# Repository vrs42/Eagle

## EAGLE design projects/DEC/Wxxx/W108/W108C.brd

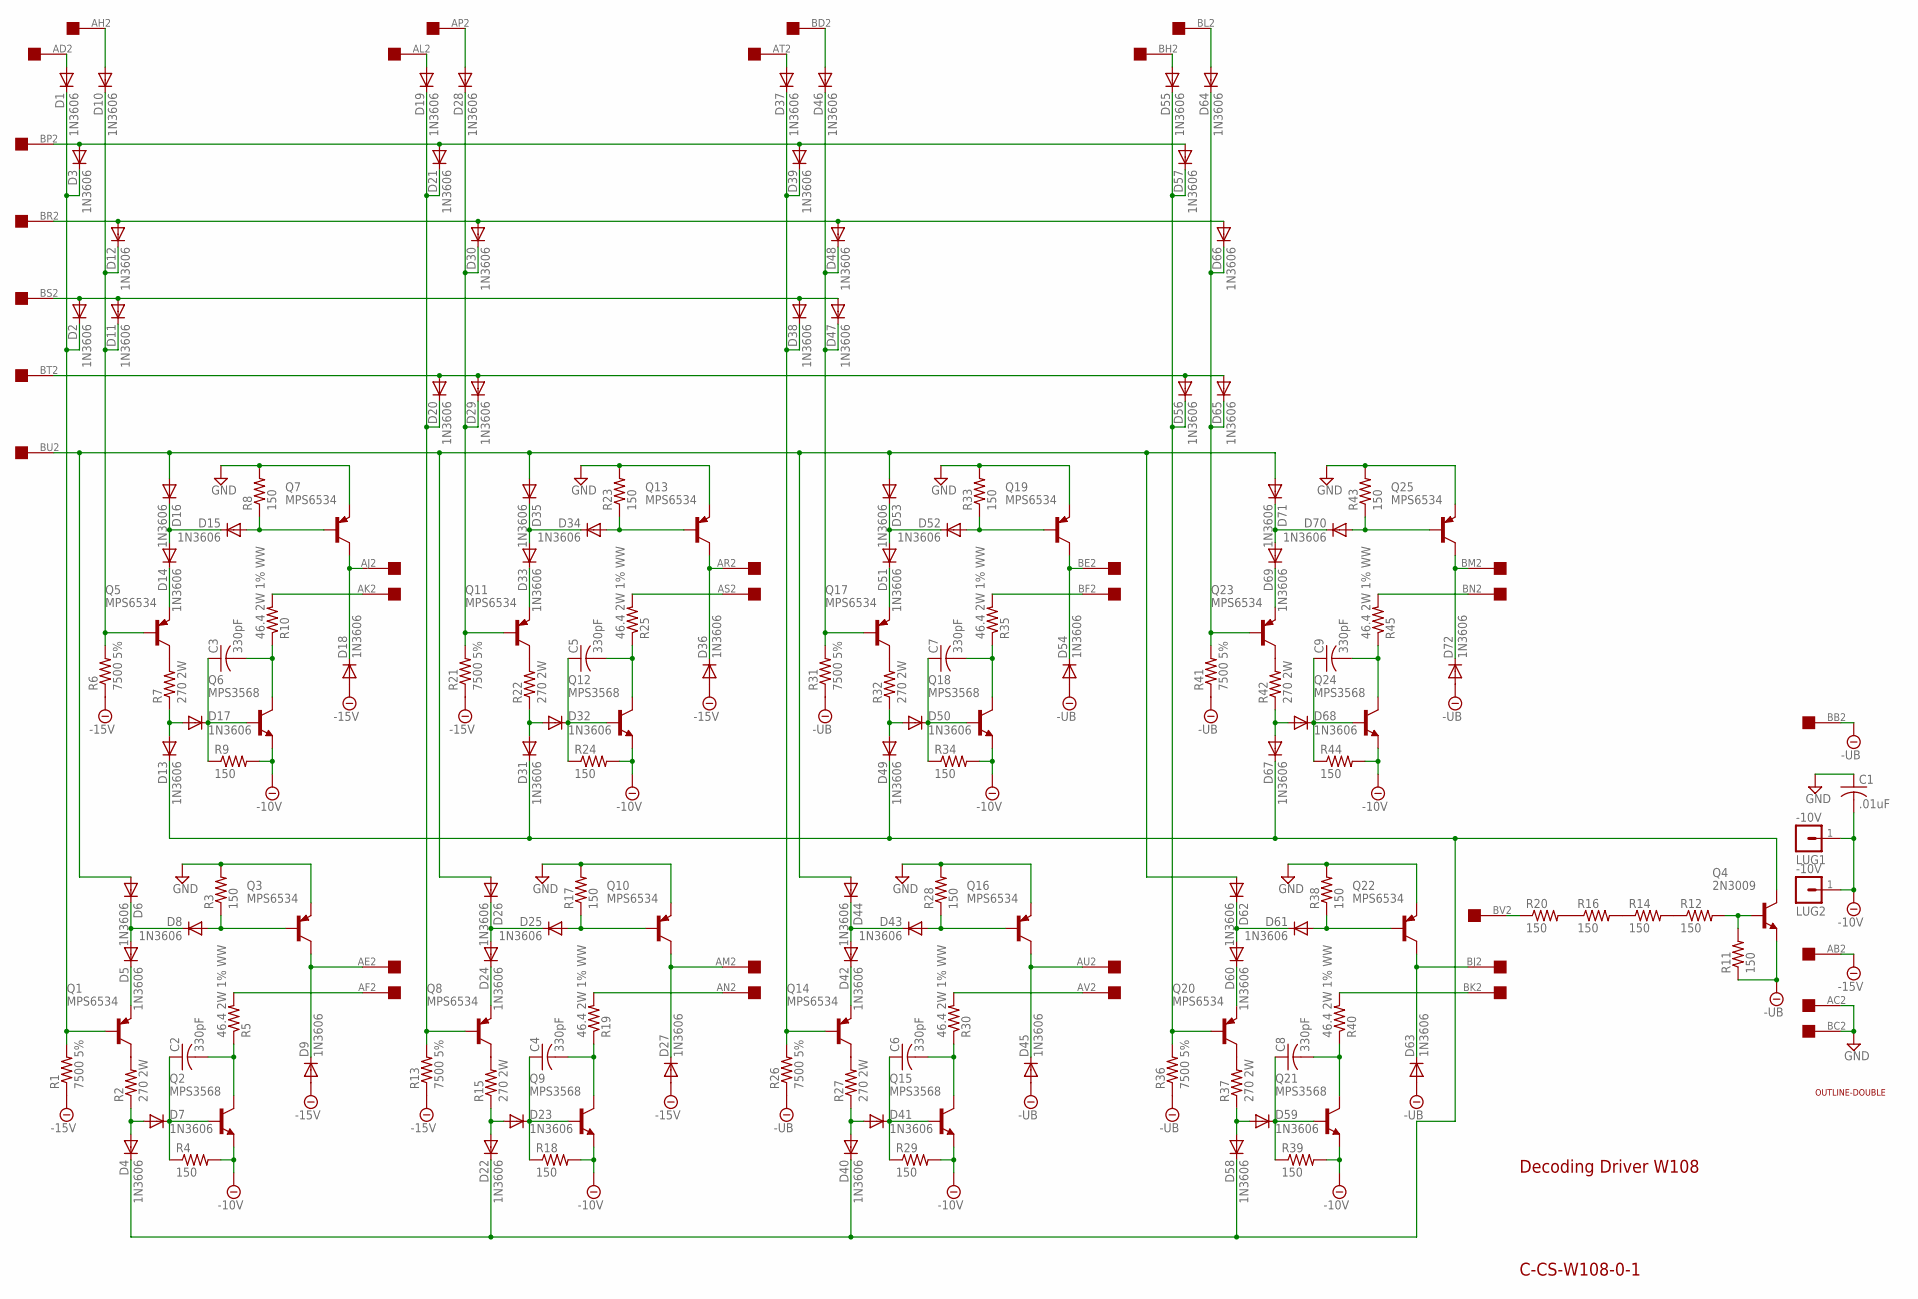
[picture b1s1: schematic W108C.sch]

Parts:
C1: .01uF; C075-032X103
C2, C3, C4, C5, C6, C7, C8, C9: 330pF; C075-032X103
D1, D2, D3, D4, D5, D6, D7, D8, D9, D10, D11, D12, D13, D14, D15, D16, D17, D18, D19, D20, D21, D22, D23, D24, D25, D26, D27, D28, D29, D30, D31, D32, D33, D34, D35, D36, D37, D38, D39, D40, D41, D42, D43, D44, D45, D46, D47, D48, D49, D50, D51, D52, D53, D54, D55, D56, D57, D58, D59, D60, D61, D62, D63, D64, D65, D66, D67, D68, D69, D70, D71, D72: 1N3606; DO35-10
LUG1, LUG2: -10V; SPADELUG
Q1, Q3, Q5, Q7, Q8, Q10, Q11, Q13, Q14, Q16, Q17, Q19, Q20, Q22, Q23, Q25: MPS6534; TO39
Q2, Q6, Q9, Q12, Q15, Q18, Q21, Q24: MPS3568; TO5
Q4: 2N3009; TO5
R1, R6, R13, R21, R26, R31, R36, R41: 7500 5%; 0207/10
R2, R7, R15, R22, R27, R32, R37, R42: 270 2W; 0617/22
R3, R4, R8, R9, R11, R12, R14, R16, R17, R18, R20, R23, R24, R28, R29, R33, R34, R38, R39, R43, R44: 150; 0207/10
R5, R10, R19, R25, R30, R35, R40, R45: 46.4 2W 1% WW; 0414/20
U$1: OUTLINE-DOUBLE; DOUBLE
U$2: DOUBLE; EDGE-CON4

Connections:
-10V: C1.2, LUG1.1, LUG2.1, Q2.1 (E), Q6.1 (E), Q9.1 (E), Q12.1 (E), Q15.1 (E), Q18.1 (E), Q21.1 (E), Q24.1 (E), R4.2, R9.2, R18.2, R24.2, R29.2, R34.2, R39.2, R44.2
-15V: D9.A, D18.A, D27.A, D36.A, R1.1, R6.1, R13.1, R21.1, U$2.AB2
-UB: D45.A, D54.A, D63.A, D72.A, Q4.1 (E), R11.1, R26.1, R31.1, R36.1, R41.1, U$2.BB2
GND: C1.1, Q3.1 (E), Q7.1 (E), Q10.1 (E), Q13.1 (E), Q16.1 (E), Q19.1 (E), Q22.1 (E), Q25.1 (E), R3.2, R8.2, R17.2, R23.2, R28.2, R33.2, R38.2, R43.2, U$2.AC2, U$2.BC2
unnamed: D1.C, D2.C, D3.C, Q1.2 (B), R1.2
unnamed: Q1.3 (C), R2.2
unnamed: D4.A, D7.A, R2.1
unnamed: C2.1, D7.C, Q2.2 (B), R4.1
unnamed: R16.1, R20.2
unnamed: C2.2, Q2.3 (C), R5.1
unnamed: R5.2, U$2.AF2
unnamed: D4.C, D13.C, D22.C, D31.C, D40.C, D49.C, D58.C, D67.C, Q4.3 (C)
unnamed: D5.C, Q1.1 (E)
unnamed: D5.A, D6.C, D8.C
unnamed: D8.A, Q3.2 (B), R3.1
unnamed: R14.1, R16.2
unnamed: D9.C, Q3.3 (C), U$2.AE2
unnamed: D1.A, U$2.AD2
unnamed: R12.1, R14.2
unnamed: D6.A, D16.A, D26.A, D35.A, D44.A, D53.A, D62.A, D71.A, U$2.BU2
unnamed: D20.A, D29.A, D56.A, D65.A, U$2.BT2
unnamed: D2.A, D11.A, D38.A, D47.A, U$2.BS2
unnamed: D3.A, D21.A, D39.A, D57.A, U$2.BP2
unnamed: D12.A, D30.A, D48.A, D66.A, U$2.BR2
unnamed: Q4.2 (B), R11.2, R12.2
unnamed: R20.1, U$2.BV2
unnamed: D55.C, D56.C, D57.C, Q20.2 (B), R36.2
unnamed: D10.C, D11.C, D12.C, Q5.2 (B), R6.2
unnamed: Q20.3 (C), R37.2
unnamed: Q5.3 (C), R7.2
unnamed: D13.A, D17.A, R7.1
unnamed: C3.1, D17.C, Q6.2 (B), R9.1
unnamed: C3.2, Q6.3 (C), R10.1
unnamed: R10.2, U$2.AK2
unnamed: D19.C, D20.C, D21.C, Q8.2 (B), R13.2
unnamed: D14.C, Q5.1 (E)
unnamed: D14.A, D15.C, D16.C
unnamed: D15.A, Q7.2 (B), R8.1
unnamed: D18.C, Q7.3 (C), U$2.AJ2
unnamed: Q8.3 (C), R15.2
unnamed: D10.A, U$2.AH2
unnamed: D22.A, D23.A, R15.1
unnamed: C4.1, D23.C, Q9.2 (B), R18.1
unnamed: C4.2, Q9.3 (C), R19.1
unnamed: R19.2, U$2.AN2
unnamed: D24.C, Q8.1 (E)
unnamed: D24.A, D25.C, D26.C
unnamed: D25.A, Q10.2 (B), R17.1
unnamed: D27.C, Q10.3 (C), U$2.AM2
unnamed: D28.C, D29.C, D30.C, Q11.2 (B), R21.2
unnamed: Q11.3 (C), R22.2
unnamed: D31.A, D32.A, R22.1
unnamed: C5.1, D32.C, Q12.2 (B), R24.1
unnamed: C5.2, Q12.3 (C), R25.1
unnamed: R25.2, U$2.AS2
unnamed: D33.C, Q11.1 (E)
unnamed: D33.A, D34.C, D35.C
unnamed: D34.A, Q13.2 (B), R23.1
unnamed: D36.C, Q13.3 (C), U$2.AR2
unnamed: D58.A, D59.A, R37.1
unnamed: C8.1, D59.C, Q21.2 (B), R39.1
unnamed: D37.C, D38.C, D39.C, Q14.2 (B), R26.2
unnamed: Q14.3 (C), R27.2
unnamed: D40.A, D41.A, R27.1
unnamed: C6.1, D41.C, Q15.2 (B), R29.1
unnamed: C6.2, Q15.3 (C), R30.1
unnamed: R30.2, U$2.AV2
unnamed: D42.C, Q14.1 (E)
unnamed: D42.A, D43.C, D44.C
unnamed: D43.A, Q16.2 (B), R28.1
unnamed: D45.C, Q16.3 (C), U$2.AU2
unnamed: D46.C, D47.C, D48.C, Q17.2 (B), R31.2
unnamed: Q17.3 (C), R32.2
unnamed: D49.A, D50.A, R32.1
unnamed: C7.1, D50.C, Q18.2 (B), R34.1
unnamed: C7.2, Q18.3 (C), R35.1
unnamed: R35.2, U$2.BF2
unnamed: D51.C, Q17.1 (E)
unnamed: D51.A, D52.C, D53.C
unnamed: D52.A, Q19.2 (B), R33.1
unnamed: D54.C, Q19.3 (C), U$2.BE2
unnamed: C8.2, Q21.3 (C), R40.1
unnamed: R40.2, U$2.BK2
unnamed: D60.C, Q20.1 (E)
unnamed: D60.A, D61.C, D62.C
unnamed: D61.A, Q22.2 (B), R38.1
unnamed: D63.C, Q22.3 (C), U$2.BJ2
unnamed: D64.C, D65.C, D66.C, Q23.2 (B), R41.2
unnamed: Q23.3 (C), R42.2
unnamed: D67.A, D68.A, R42.1
unnamed: C9.1, D68.C, Q24.2 (B), R44.1
unnamed: C9.2, Q24.3 (C), R45.1
unnamed: R45.2, U$2.BN2
unnamed: D69.C, Q23.1 (E)
unnamed: D69.A, D70.C, D71.C
unnamed: D70.A, Q25.2 (B), R43.1
unnamed: D72.C, Q25.3 (C), U$2.BM2
unnamed: D19.A, U$2.AL2
unnamed: D28.A, U$2.AP2
unnamed: D37.A, U$2.AT2
unnamed: D46.A, U$2.BD2
unnamed: D55.A, U$2.BH2
unnamed: D64.A, U$2.BL2

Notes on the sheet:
Decoding Driver W108
C-CS-W108-0-1

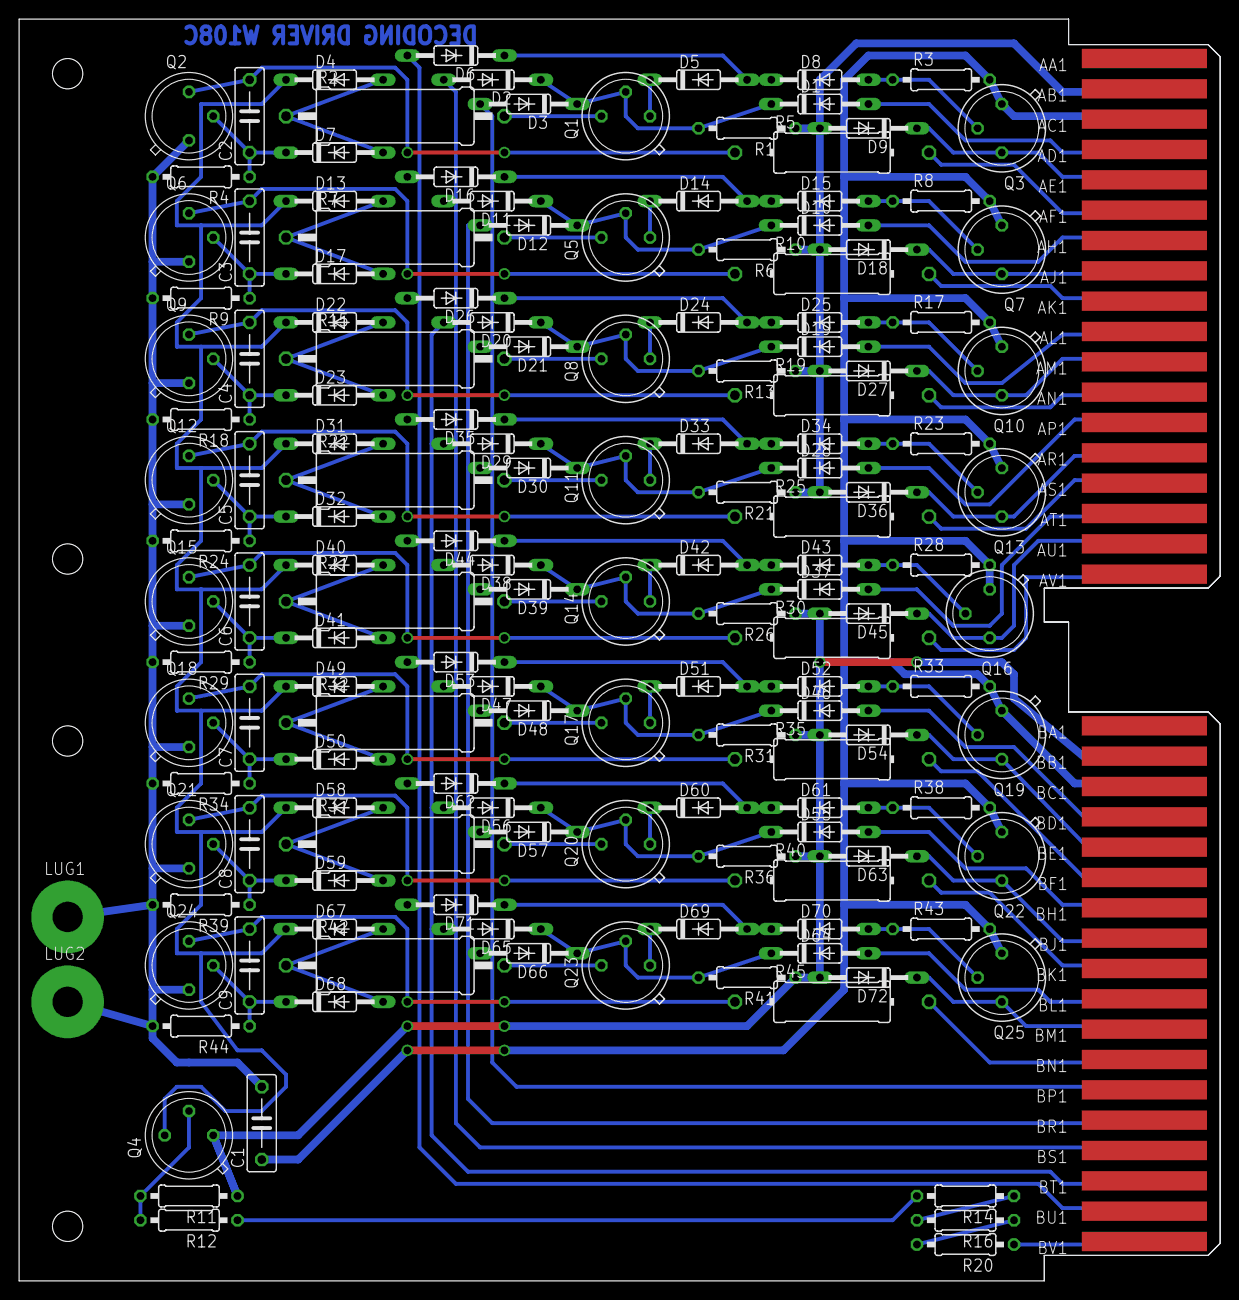
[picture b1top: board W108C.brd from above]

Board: 2 copper layers, 125.7 x 132.1 mm, 155 parts (0 on the bottom side), 103 nets.

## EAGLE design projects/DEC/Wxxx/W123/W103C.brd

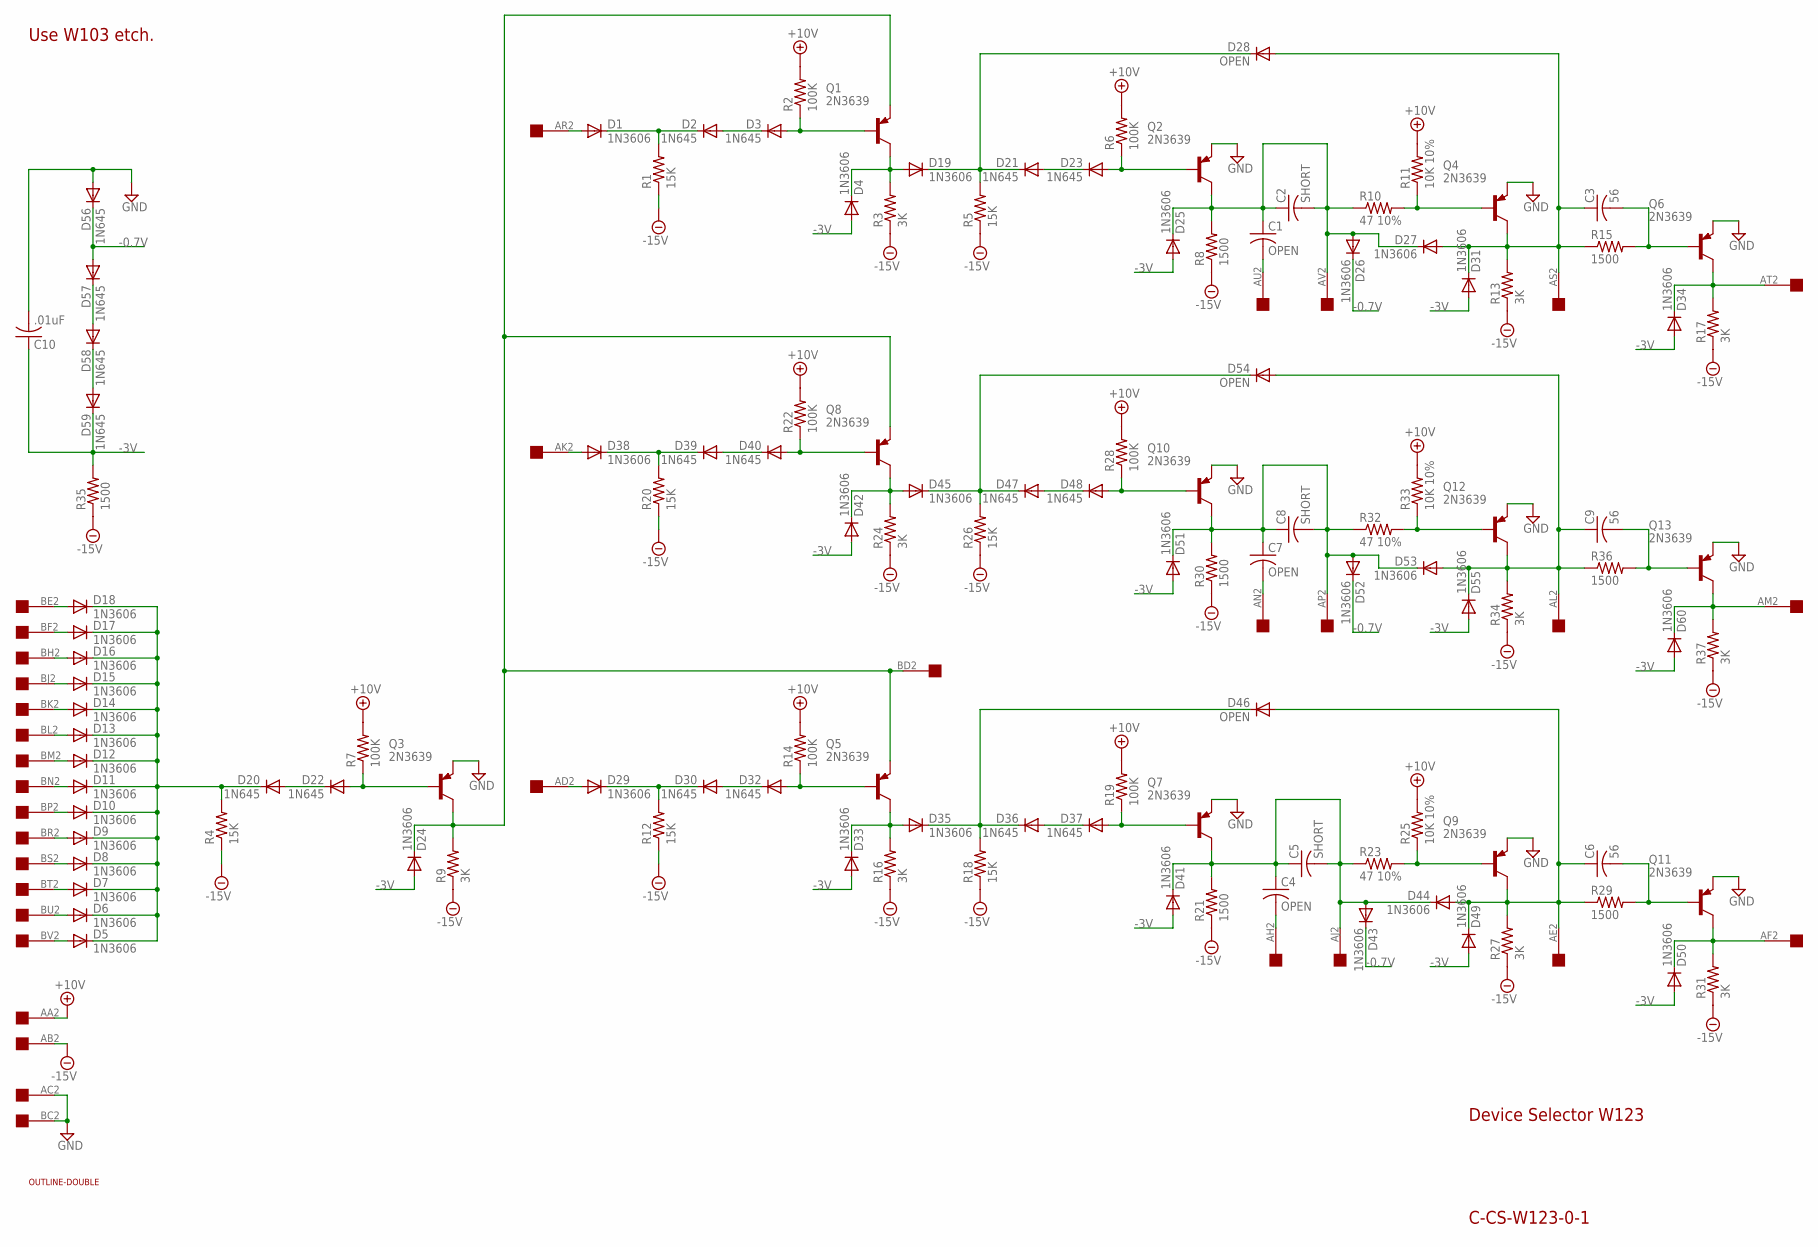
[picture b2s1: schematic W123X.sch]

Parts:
C1, C4, C7: OPEN; C075-032X103
C2, C5, C8: SHORT; C075-032X103
C3, C6, C9: 56; C075-032X103
C10: .01uF; C075-032X103
D1, D4, D5, D6, D7, D8, D9, D10, D11, D12, D13, D14, D15, D16, D17, D18, D19, D24, D25, D26, D27, D29, D31, D33, D34, D35, D38, D41, D42, D43, D44, D45, D49, D50, D51, D52, D53, D55, D60: 1N3606; DO35-10
D2, D3, D20, D21, D22, D23, D30, D32, D36, D37, D39, D40, D47, D48, D56, D57, D58, D59: 1N645; DO35-10
D28, D46, D54: OPEN; DO35-10
Q1, Q2, Q3, Q4, Q5, Q6, Q7, Q8, Q9, Q10, Q11, Q12, Q13: 2N3639; TO39
R1, R4, R5, R12, R18, R20, R26: 15K; 0207/10
R2, R6, R7, R14, R19, R22, R28: 100K; 0207/10
R3, R9, R13, R16, R17, R24, R27, R31, R34, R37: 3K; 0207/10
R8, R15, R21, R29, R30, R35, R36: 1500; 0207/10
R10, R23, R32: 47 10%; 0207/10
R11, R25, R33: 10K 10%; 0207/10
U$1: OUTLINE-DOUBLE; DOUBLE
U$2: DOUBLE; EDGE-CON4

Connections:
+10V: R2.2, R6.2, R7.2, R11.2, R14.2, R19.2, R22.2, R25.2, R28.2, R33.2, U$2.AA2
-0.7V: D26.C, D43.C, D52.C, D56.C, D57.A
-3V: C10.1, D4.A, D24.A, D25.A, D31.A, D33.A, D34.A, D41.A, D42.A, D49.A, D50.A, D51.A, D55.A, D59.C, D60.A, R35.2
-15V: R1.1, R3.1, R4.1, R5.1, R8.1, R9.1, R12.1, R13.1, R16.1, R17.1, R18.1, R20.1, R21.1, R24.1, R26.1, R27.1, R30.1, R31.1, R34.1, R35.1, R37.1, U$2.AB2
GND: C10.2, D56.A, Q2.1 (E), Q3.1 (E), Q4.1 (E), Q6.1 (E), Q7.1 (E), Q9.1 (E), Q10.1 (E), Q11.1 (E), Q12.1 (E), Q13.1 (E), U$2.AC2, U$2.BC2
unnamed: D14.A, U$2.BK2
unnamed: D15.A, U$2.BJ2
unnamed: D16.A, U$2.BH2
unnamed: D17.A, U$2.BF2
unnamed: D18.A, U$2.BE2
unnamed: D13.A, U$2.BL2
unnamed: D5.A, U$2.BV2
unnamed: D6.A, U$2.BU2
unnamed: D7.A, U$2.BT2
unnamed: D8.A, U$2.BS2
unnamed: D9.A, U$2.BR2
unnamed: D10.A, U$2.BP2
unnamed: D11.A, U$2.BN2
unnamed: D12.A, U$2.BM2
unnamed: D5.C, D6.C, D7.C, D8.C, D9.C, D10.C, D11.C, D12.C, D13.C, D14.C, D15.C, D16.C, D17.C, D18.C, D20.C, R4.2
unnamed: D20.A, D22.C
unnamed: D22.A, Q3.2 (B), R7.1
unnamed: D24.C, Q1.1 (E), Q3.3 (C), Q5.1 (E), Q8.1 (E), R9.2, U$2.BD2
unnamed: D29.A, U$2.AD2
unnamed: D29.C, D30.C, R12.2
unnamed: D30.A, D32.C
unnamed: D32.A, Q5.2 (B), R14.1
unnamed: D33.C, D35.A, Q5.3 (C), R16.2
unnamed: D1.A, U$2.AR2
unnamed: D35.C, D36.C, D46.C, R18.2
unnamed: D36.A, D37.C
unnamed: D37.A, Q7.2 (B), R19.1
unnamed: C4.2, U$2.AH2
unnamed: Q9.2 (B), R23.2, R25.1
unnamed: C6.1, D44.A, D46.A, D49.C, Q9.3 (C), R27.2, R29.1, U$2.AE2
unnamed: C6.2, Q11.2 (B), R29.2
unnamed: D50.C, Q11.3 (C), R31.2, U$2.AF2
unnamed: D1.C, D2.C, R1.2
unnamed: D2.A, D3.C
unnamed: D3.A, Q1.2 (B), R2.1
unnamed: D4.C, D19.A, Q1.3 (C), R3.2
unnamed: D19.C, D21.C, D28.C, R5.2
unnamed: D21.A, D23.C
unnamed: D23.A, Q2.2 (B), R6.1
unnamed: D38.A, U$2.AK2
unnamed: C1.2, U$2.AU2
unnamed: Q4.2 (B), R10.2, R11.1
unnamed: C3.1, D27.A, D28.A, D31.C, Q4.3 (C), R13.2, R15.1, U$2.AS2
unnamed: C3.2, Q6.2 (B), R15.2
unnamed: D34.C, Q6.3 (C), R17.2, U$2.AT2
unnamed: D38.C, D39.C, R20.2
unnamed: D39.A, D40.C
unnamed: D40.A, Q8.2 (B), R22.1
unnamed: D42.C, D45.A, Q8.3 (C), R24.2
unnamed: D45.C, D47.C, D54.C, R26.2
unnamed: D47.A, D48.C
unnamed: D48.A, Q10.2 (B), R28.1
unnamed: C7.2, U$2.AN2
unnamed: Q12.2 (B), R32.2, R33.1
unnamed: C9.1, D53.A, D54.A, D55.C, Q12.3 (C), R34.2, R36.1, U$2.AL2
unnamed: C9.2, Q13.2 (B), R36.2
unnamed: D60.C, Q13.3 (C), R37.2, U$2.AM2
unnamed: D58.C, D59.A
unnamed: D57.C, D58.A

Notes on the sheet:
Device Selector W123
C-CS-W123-0-1
Use W103 etch.

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
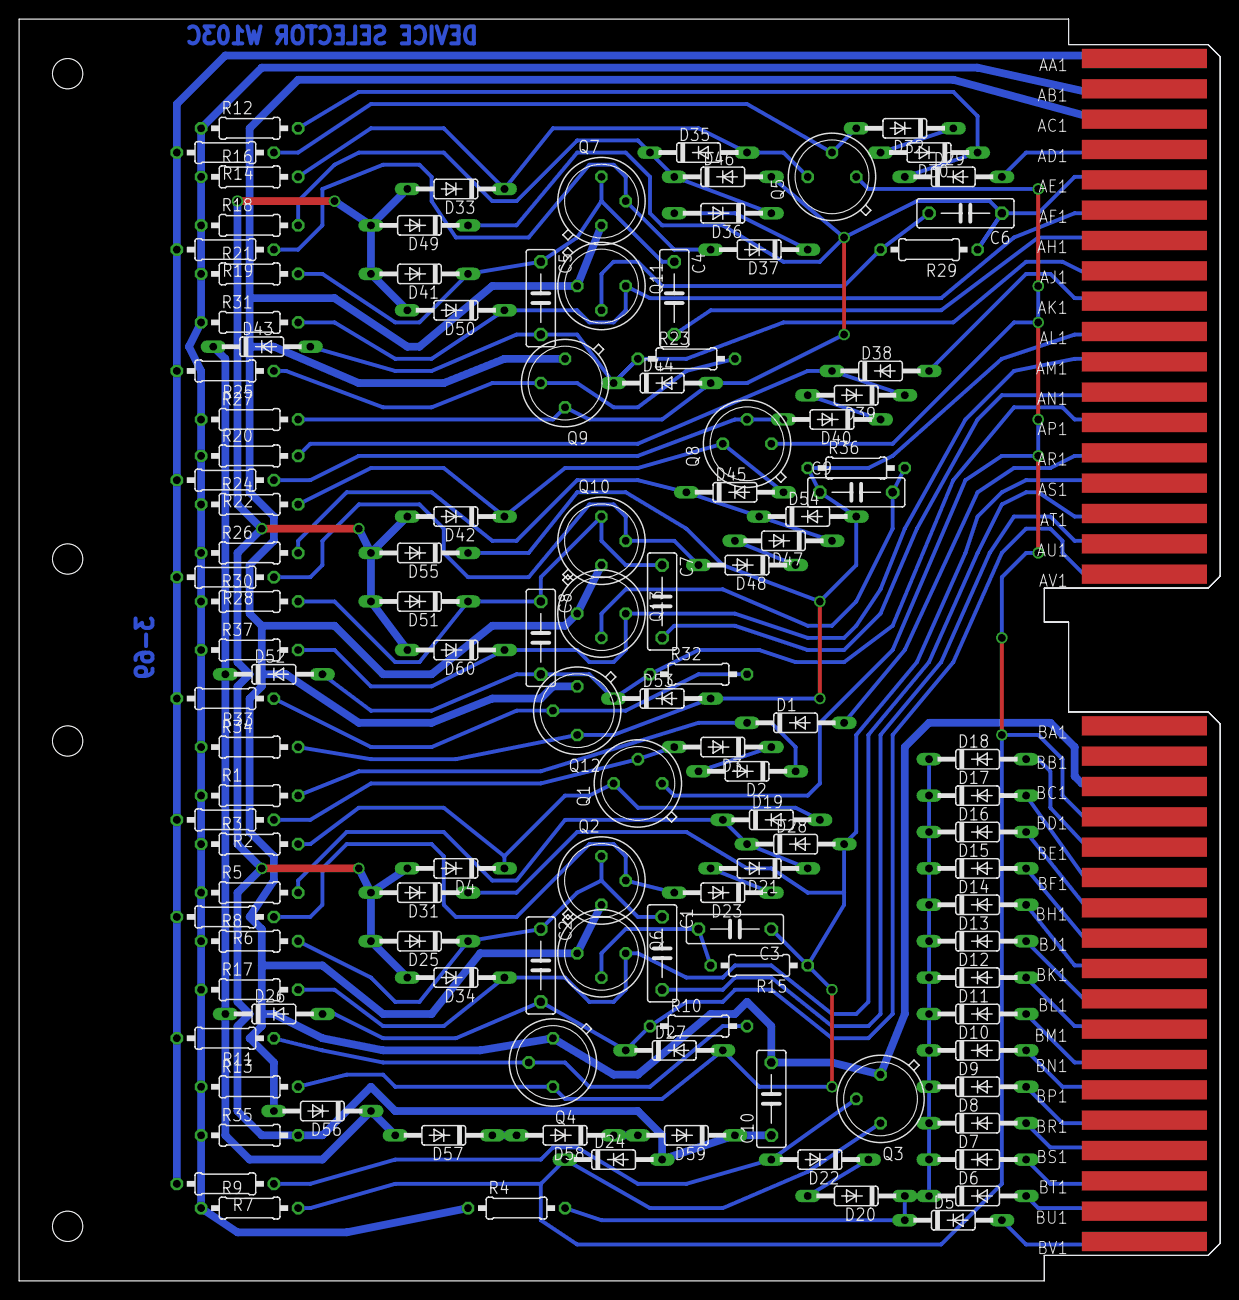
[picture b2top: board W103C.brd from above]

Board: 2 copper layers, 125.7 x 132.1 mm, 122 parts (0 on the bottom side), 70 nets.

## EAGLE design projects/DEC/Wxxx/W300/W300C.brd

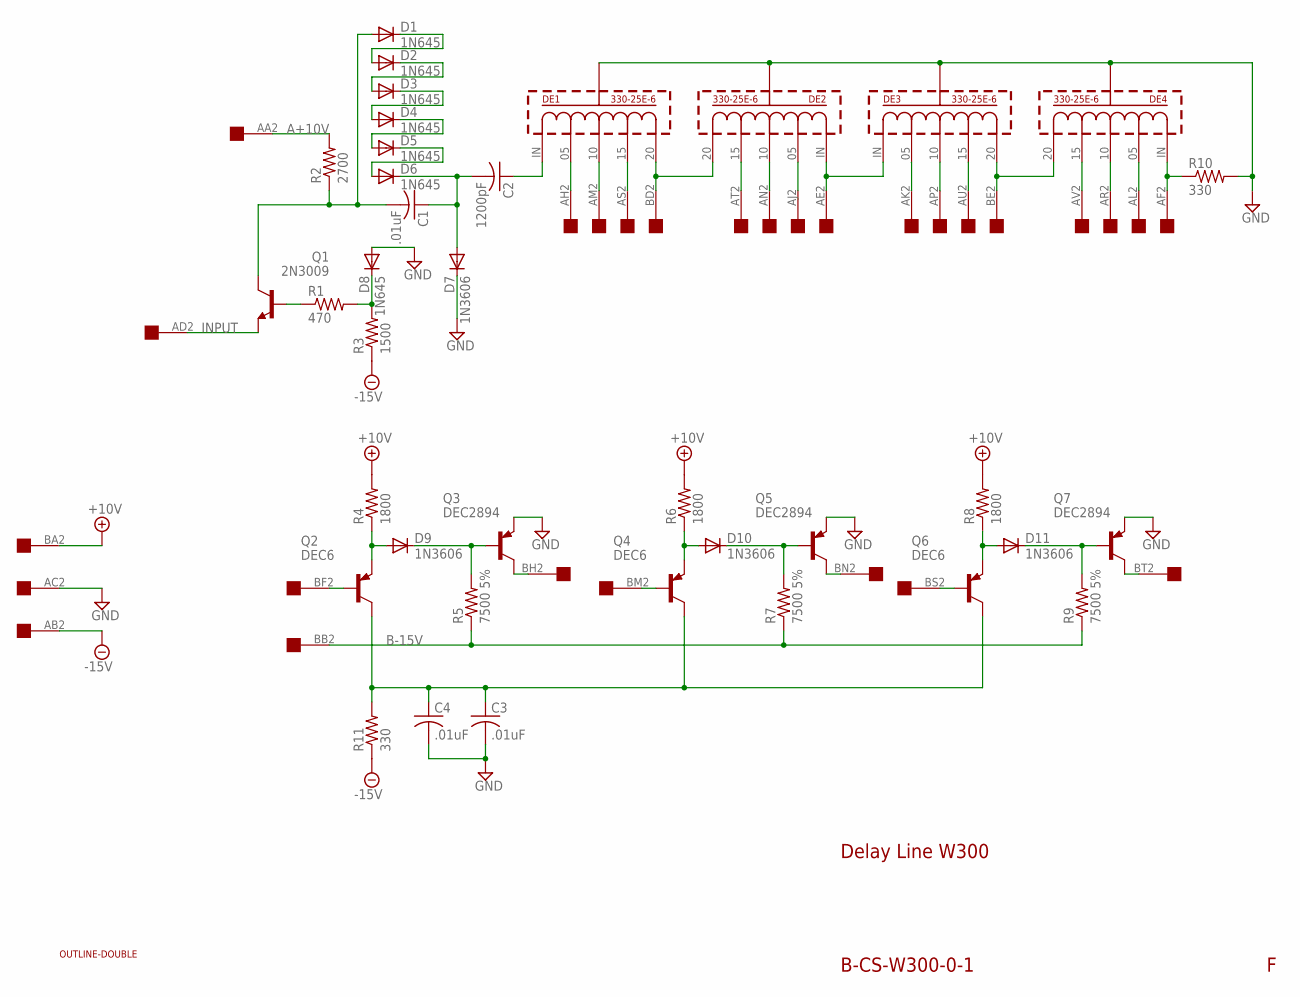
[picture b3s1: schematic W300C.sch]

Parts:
C1, C3, C4: .01uF; C050-025X075
C2: 1200pF; C102-043X133
D1, D2, D3, D4, D5, D6, D8: 1N645; DO35-10
D7, D9, D10, D11: 1N3606; DO35-10
DE1, DE2, DE3, DE4: 330-25E-6; 330-25E
Q1: 2N3009; TO5
Q2, Q4, Q6: DEC6; TO5
Q3, Q5, Q7: DEC2894; TO5
R1: 470; 0207/10
R2: 2700; 0207/10
R3: 1500; 0207/10
R4, R6, R8: 1800; 0207/10
R5, R7, R9: 7500 5%; 0207/10
R10, R11: 330; 0207/10
U$1: OUTLINE-DOUBLE; DOUBLE
U$3: DOUBLE; EDGE-CON4

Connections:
+10V: R4.2, R6.2, R8.2, U$3.BA2
-15V: R3.1, R11.1, U$3.AB2
A+10V: R2.2, U$3.AA2
B-15V: R5.1, R7.1, R9.1, U$3.BB2
GND: C3.2, C4.2, D7.C, D8.A, DE1.GND, DE2.GND, DE3.GND, DE4.GND, Q3.1 (E), Q5.1 (E), Q7.1 (E), R10.2, U$3.AC2
INPUT: Q1.1 (E), U$3.AD2
unnamed: DE1.05 (5), U$3.AH2
unnamed: DE1.10, U$3.AM2
unnamed: DE1.15, U$3.AS2
unnamed: DE1.20, DE2.20, U$3.BD2
unnamed: DE2.15, U$3.AT2
unnamed: DE2.10, U$3.AN2
unnamed: DE2.05 (5), U$3.AJ2
unnamed: DE2.IN (0), DE3.IN (0), U$3.AE2
unnamed: DE3.05 (5), U$3.AK2
unnamed: DE3.10, U$3.AP2
unnamed: DE3.15, U$3.AU2
unnamed: DE3.20, DE4.20, U$3.BE2
unnamed: DE4.15, U$3.AV2
unnamed: DE4.10, U$3.AR2
unnamed: DE4.05 (5), U$3.AL2
unnamed: DE4.IN (0), R10.1, U$3.AF2
unnamed: C2.1, DE1.IN (0)
unnamed: Q1.2 (B), R1.1
unnamed: D8.C, R1.2, R3.2
unnamed: C1.1, C2.2, D6.C, D7.A
unnamed: D5.C, D6.A
unnamed: D4.C, D5.A
unnamed: D3.C, D4.A
unnamed: D1.C, D2.A
unnamed: D2.C, D3.A
unnamed: C1.2, D1.A, Q1.3 (C), R2.1
unnamed: Q2.2 (B), U$3.BF2
unnamed: C3.1, C4.1, Q2.3 (C), Q4.3 (C), Q6.3 (C), R11.2
unnamed: D9.A, Q2.1 (E), R4.1
unnamed: D9.C, Q3.2 (B), R5.2
unnamed: Q3.3 (C), U$3.BH2
unnamed: Q4.2 (B), U$3.BM2
unnamed: D10.A, Q4.1 (E), R6.1
unnamed: D10.C, Q5.2 (B), R7.2
unnamed: Q5.3 (C), U$3.BN2
unnamed: Q6.2 (B), U$3.BS2
unnamed: D11.A, Q6.1 (E), R8.1
unnamed: D11.C, Q7.2 (B), R9.2
unnamed: Q7.3 (C), U$3.BT2

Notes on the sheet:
Delay Line W300
B-CS-W300-0-1

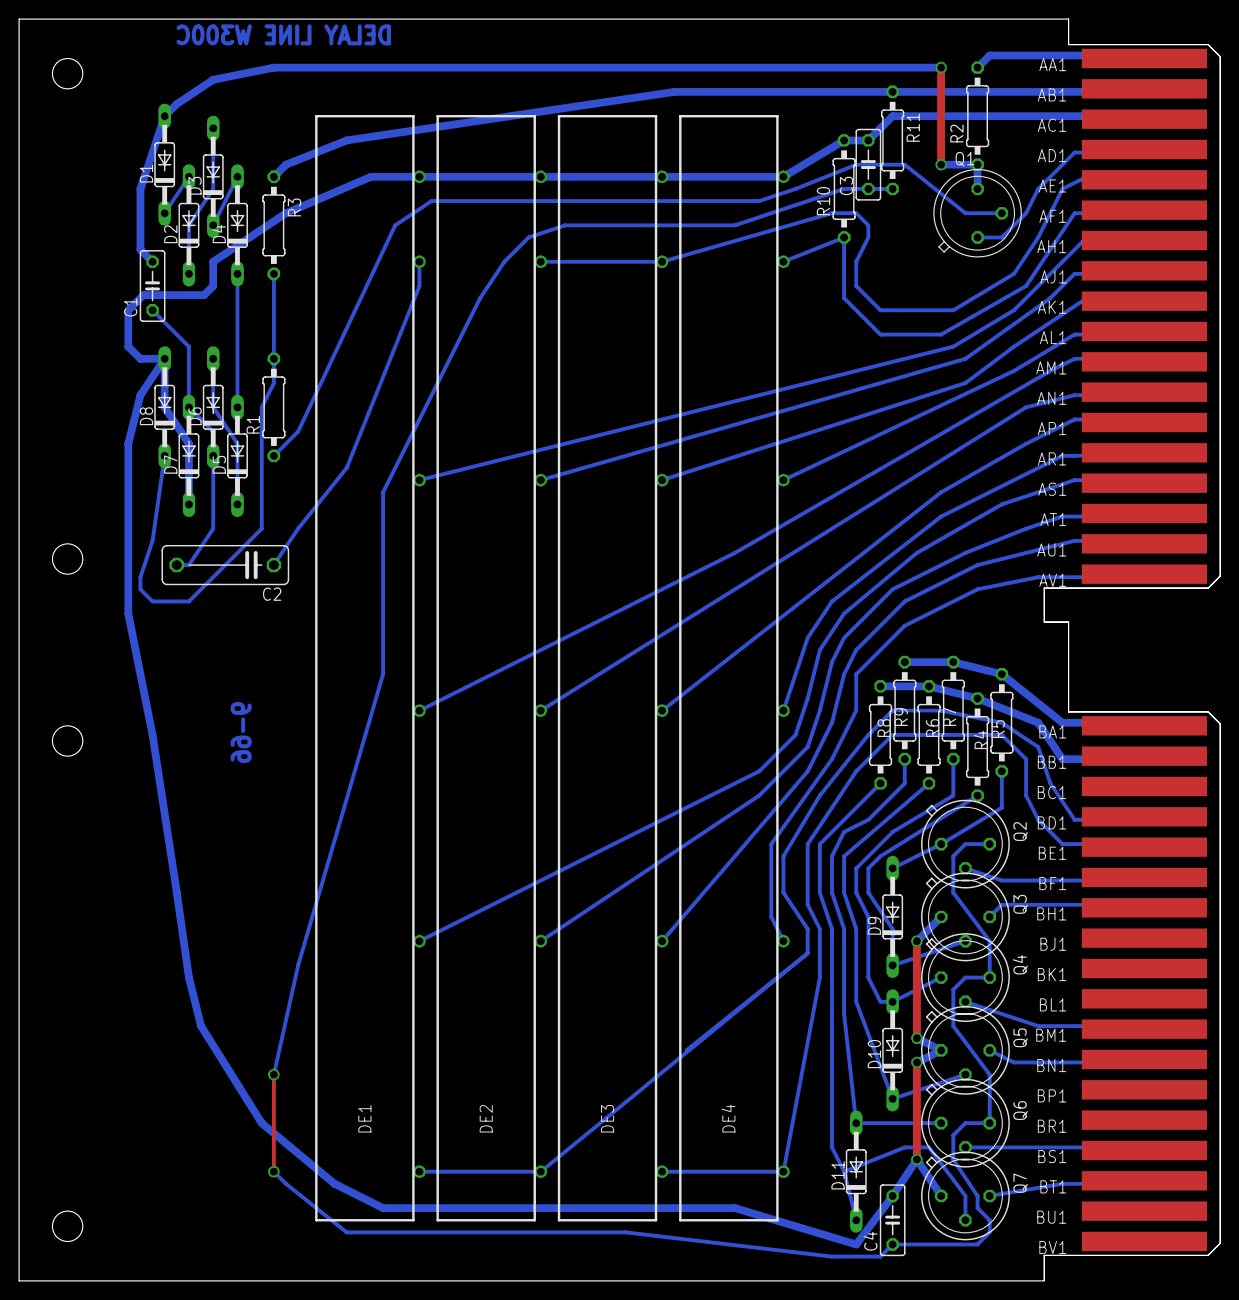
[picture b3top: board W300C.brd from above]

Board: 2 copper layers, 125.7 x 132.1 mm, 39 parts (0 on the bottom side), 45 nets.

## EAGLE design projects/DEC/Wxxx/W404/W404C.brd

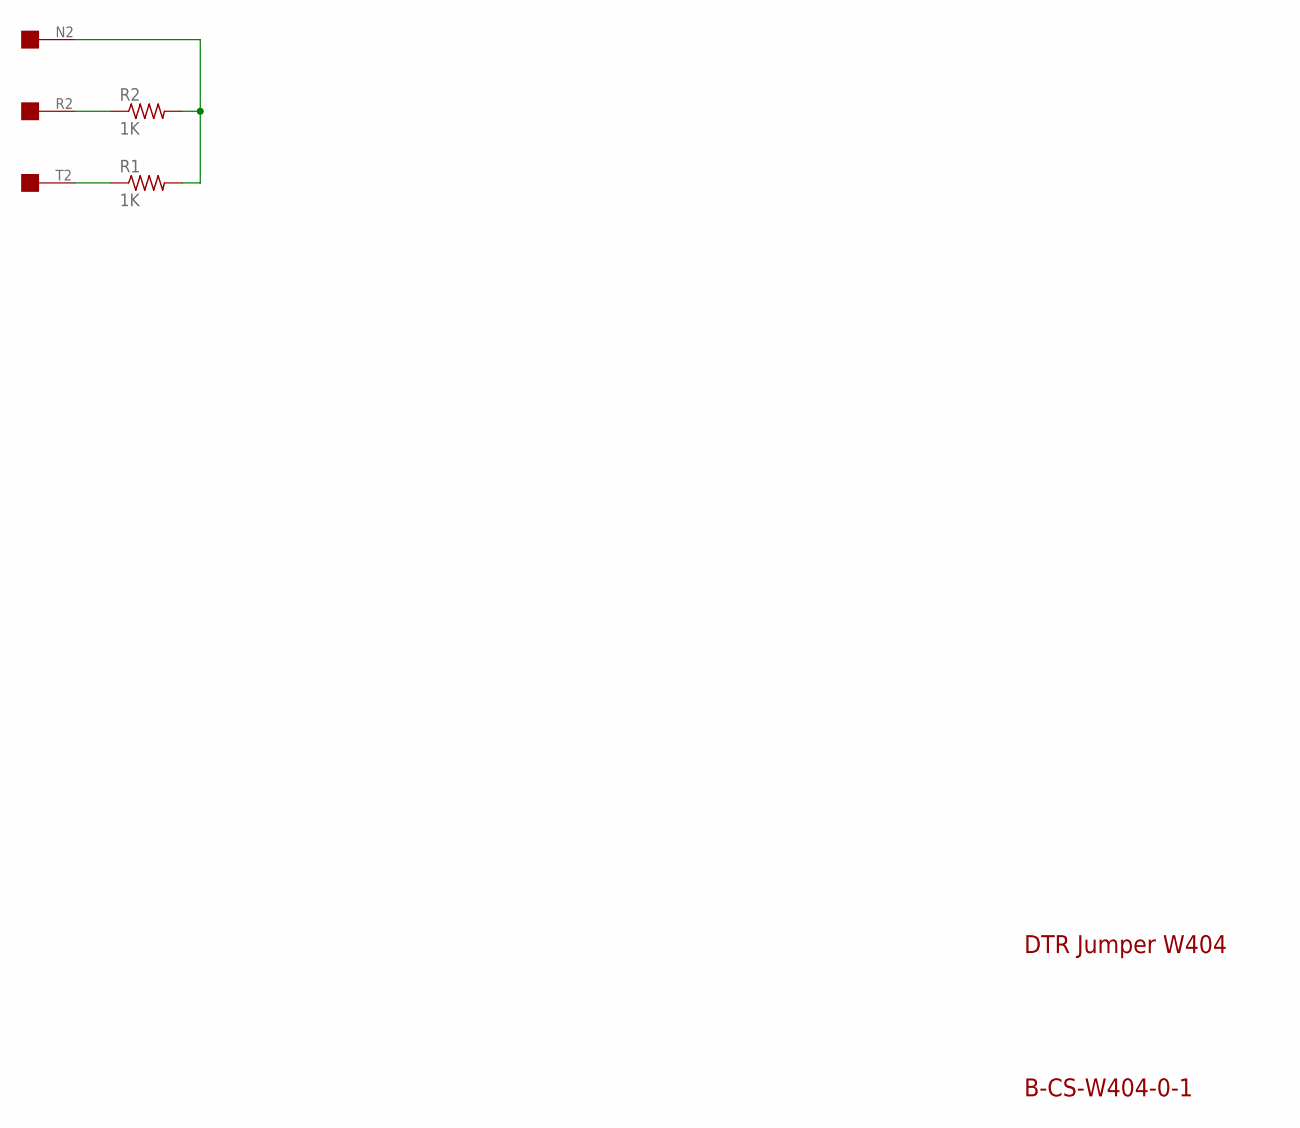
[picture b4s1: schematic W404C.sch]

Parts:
R1, R2: 1K; 0818/25
U$2: EDGE-1; EDGE-CON1

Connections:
unnamed: R1.2, R2.2, U$2.N2
unnamed: R2.1, U$2.R2
unnamed: R1.1, U$2.T2

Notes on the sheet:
DTR Jumper W404
B-CS-W404-0-1

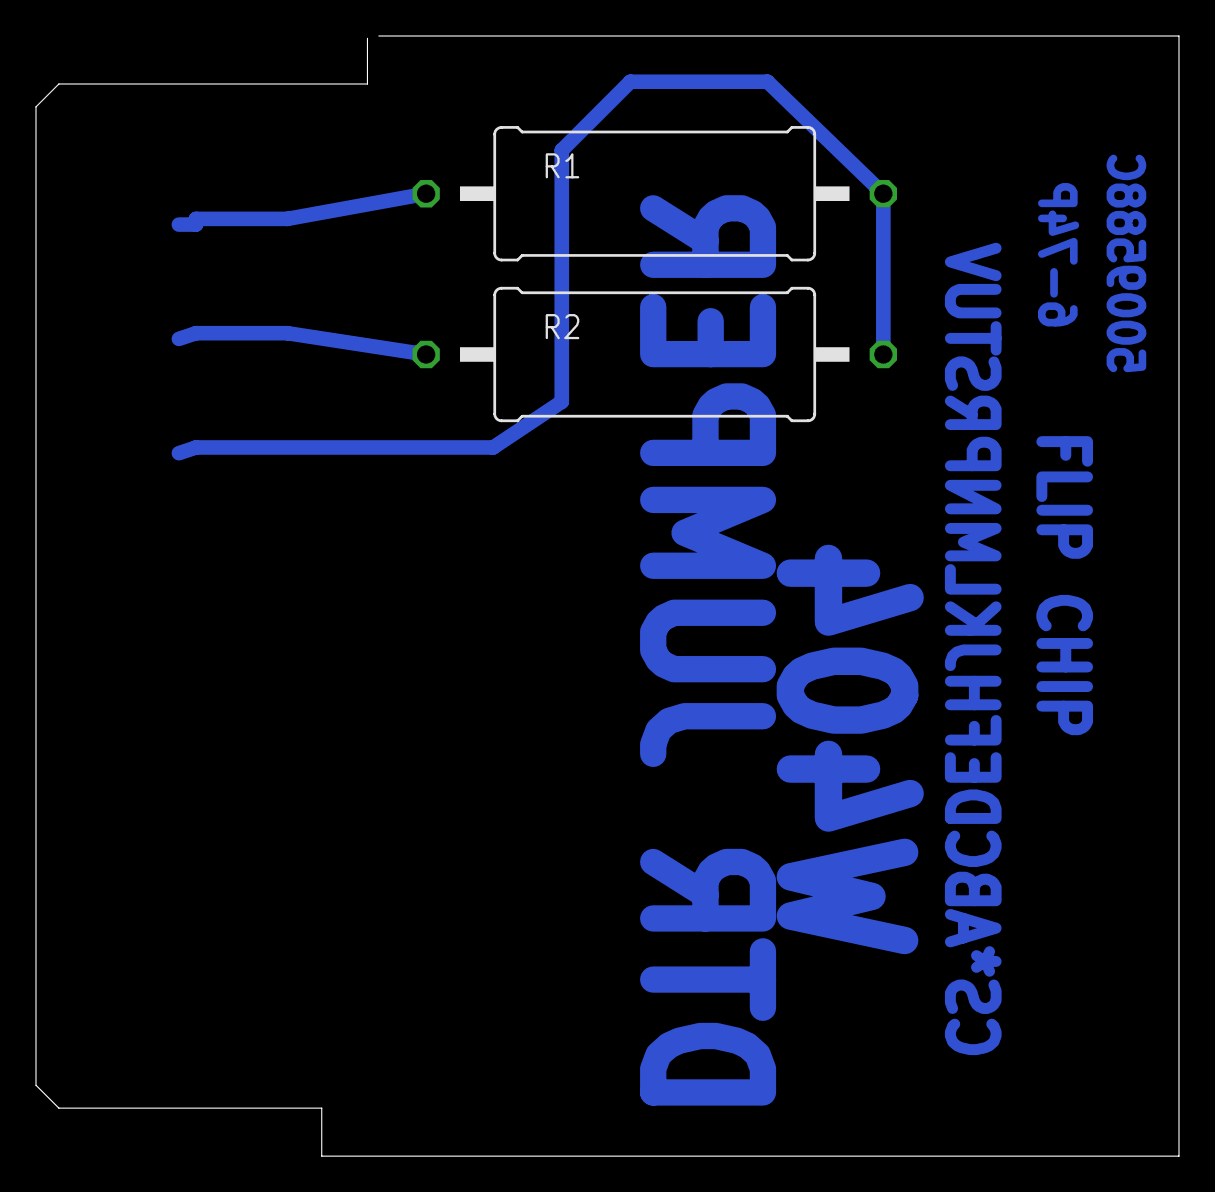
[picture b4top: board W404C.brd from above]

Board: 2 copper layers, 63.5 x 62.2 mm, 3 parts (0 on the bottom side), 3 nets.
